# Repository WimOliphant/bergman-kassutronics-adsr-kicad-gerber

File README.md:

# bergman-kassutronics-adsr-kicad-gerber

KiCad project file and gerbers for ADSR envelope generator. 

https://www.eddybergman.com/2025/04/Kassutronic-precision-adsr.html

Currently untested. It may not work!!!

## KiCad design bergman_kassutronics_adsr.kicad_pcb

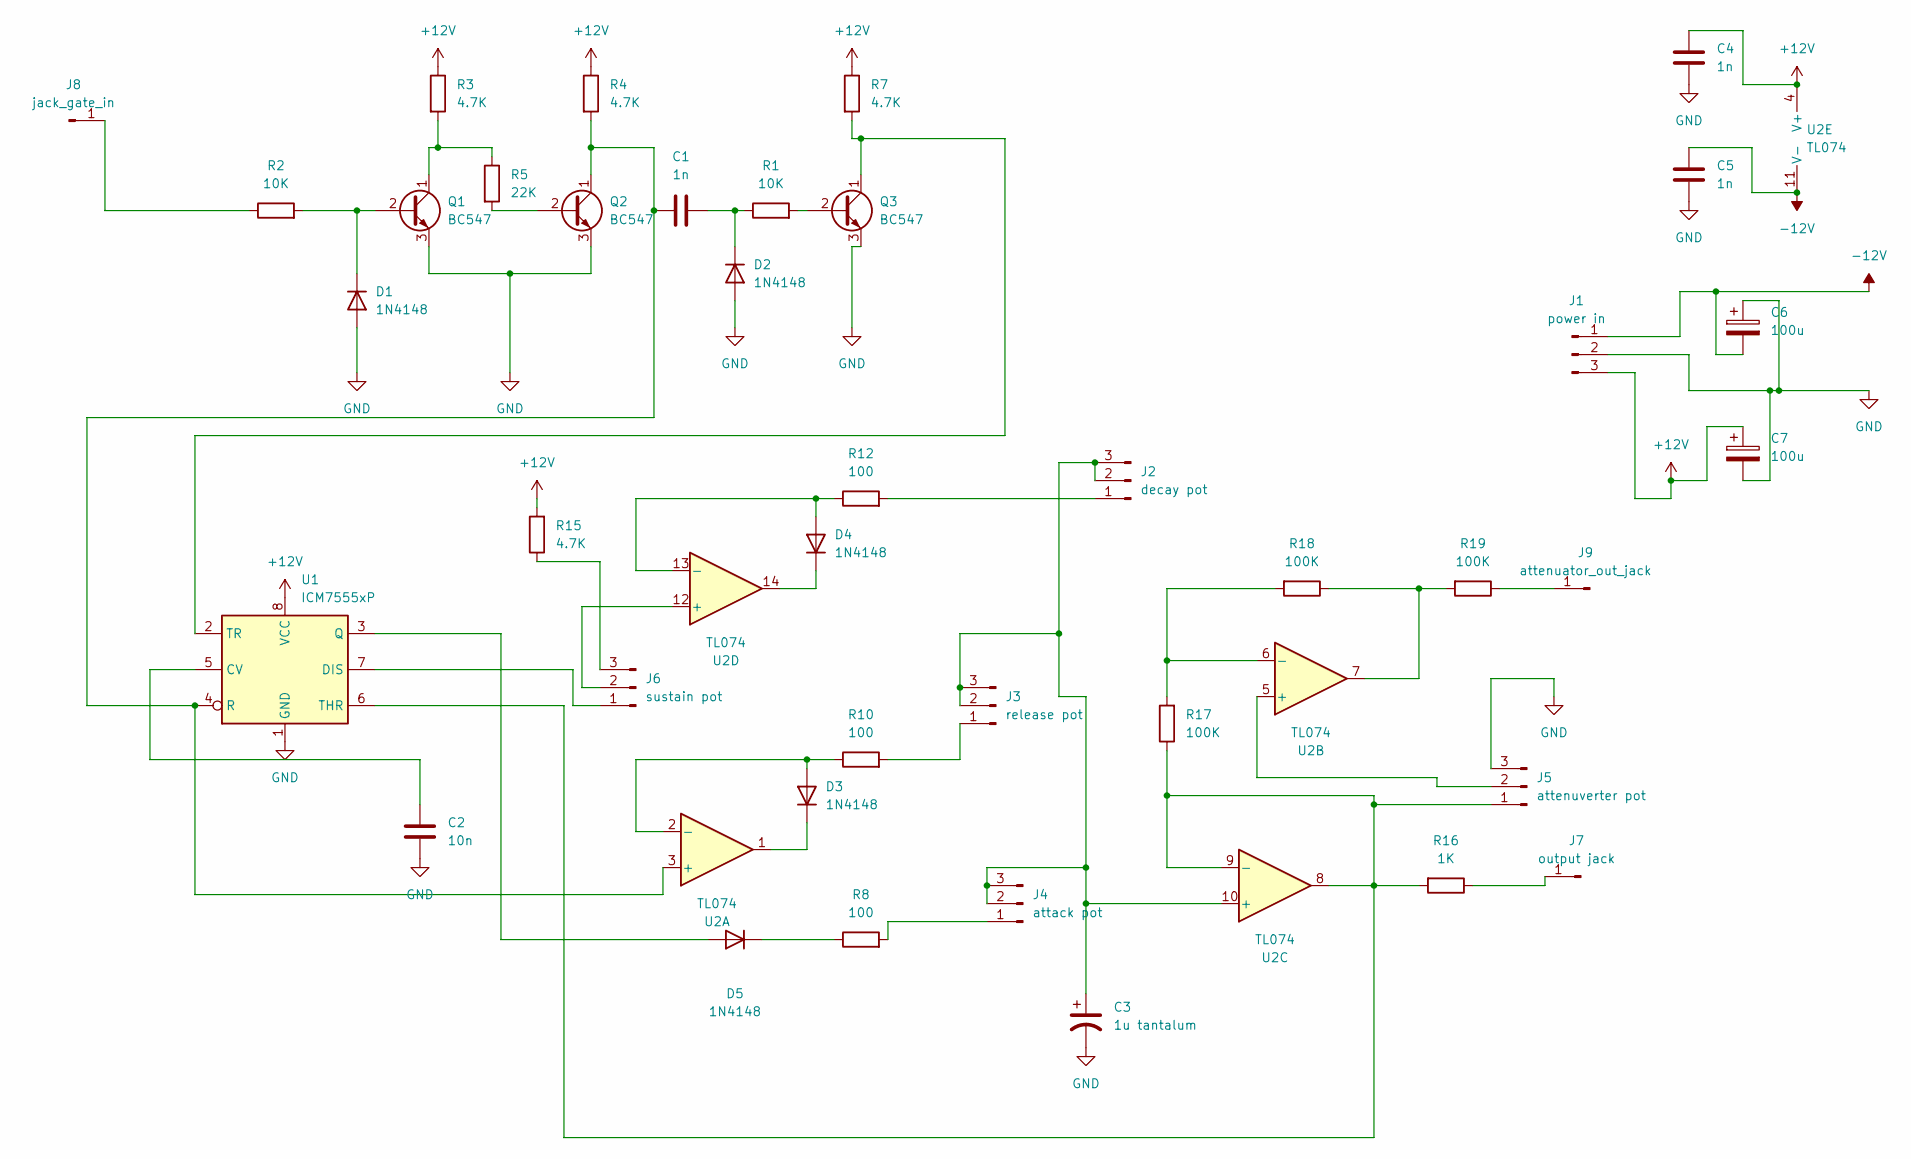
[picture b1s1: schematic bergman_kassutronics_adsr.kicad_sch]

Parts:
C1, C4, C5: 1n; C_Disc_D3.8mm_W2.6mm_P2.50mm
C2: 10n; C_Disc_D3.8mm_W2.6mm_P2.50mm
C3: 1u tantalum; C_Rect_L4.6mm_W3.8mm_P2.50mm_MKS02_FKP02
C6, C7: 100u; CP_Radial_D5.0mm_P2.50mm
D1, D2, D3, D4, D5: 1N4148; D_DO-35_SOD27_P7.62mm_Horizontal
J1: power in; Samtec_HPM-03-01-x-S_Straight_1x03_Pitch5.08mm
J2: decay pot; PinHeader_1x03_P2.54mm_Vertical
J3: release pot; PinHeader_1x03_P2.54mm_Vertical
J4: attack pot; PinHeader_1x03_P2.54mm_Vertical
J5: attenuverter pot; PinHeader_1x03_P2.54mm_Vertical
J6: sustain pot; PinHeader_1x03_P2.54mm_Vertical
J7: output jack; PinHeader_1x01_P2.54mm_Vertical
J8: jack_gate_in; PinHeader_1x01_P2.54mm_Vertical
J9: attenuator_out_jack; PinHeader_1x01_P2.54mm_Vertical
Q1, Q2, Q3: BC547; TO-92L_Inline_Wide
R1, R2: 10K; R_Axial_DIN0204_L3.6mm_D1.6mm_P7.62mm_Horizontal_wims_resis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
R3, R4, R7, R15: 4.7K; R_Axial_DIN0204_L3.6mm_D1.6mm_P7.62mm_Horizontal_wims_resis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
R5: 22K; R_Axial_DIN0204_L3.6mm_D1.6mm_P7.62mm_Horizontal_wims_resis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
R8, R10, R12: 100; R_Axial_DIN0204_L3.6mm_D1.6mm_P7.62mm_Horizontal_wims_resis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
R16: 1K; R_Axial_DIN0204_L3.6mm_D1.6mm_P7.62mm_Horizontal_wims_resis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
R17, R18, R19: 100K; R_Axial_DIN0204_L3.6mm_D1.6mm_P7.62mm_Horizontal_wims_resis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
U1: ICM7555xP; DIP-8_W7.62mm_LongPads
U2: TL074; DIP-14_W7.62mm_LongPads

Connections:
+12V: C4.1, C7.1, J1.3, R3.1, R4.1, R7.1, R15.2, U1.8 (VCC), U2.4 (V+)
-12V: C5.1, C6.2, J1.1, U2.11 (V-)
GND: C2.2, C3.2, C4.2, C5.2, C6.1, C7.2, D1.2 (A), D2.2 (A), J1.2, J5.3, Q1.3 (E), Q2.3 (E), Q3.3 (E), U1.1 (GND)
unnamed: D1.1 (K), Q1.2 (B), R2.2
unnamed: C1.2, D2.1 (K), R1.1
unnamed: D3.2 (A), R10.1, U2.2 (-)
unnamed: D3.1 (K), U2.1
unnamed: D4.2 (A), R12.1, U2.13 (-)
unnamed: D4.1 (K), U2.14
unnamed: D5.2 (A), U1.3 (Q)
unnamed: D5.1 (K), R8.1
unnamed: J2.1, R12.2
unnamed: C3.1, J2.2, J2.3, J3.2, J3.3, J4.2, J4.3, U2.10 (+)
unnamed: J3.1, R10.2
unnamed: J4.1, R8.2
unnamed: J5.1, R16.2, R17.1, U1.6 (THR), U2.8, U2.9 (-)
unnamed: J5.2, U2.5 (+)
unnamed: J6.1, U1.7 (DIS)
unnamed: J6.2, U2.12 (+)
unnamed: J6.3, R15.1
unnamed: J7.1, R16.1
unnamed: J8.1, R2.1
unnamed: J9.1, R19.1
unnamed: Q1.1 (C), R3.2, R5.1
unnamed: Q2.2 (B), R5.2
unnamed: C1.1, Q2.1 (C), R4.2, U1.4 (R), U2.3 (+)
unnamed: Q3.2 (B), R1.2
unnamed: Q3.1 (C), R7.2, U1.2 (TR)
unnamed: R18.1, R19.2, U2.7
unnamed: C2.1, U1.5 (CV)
unnamed: R17.2, R18.2, U2.6 (-)

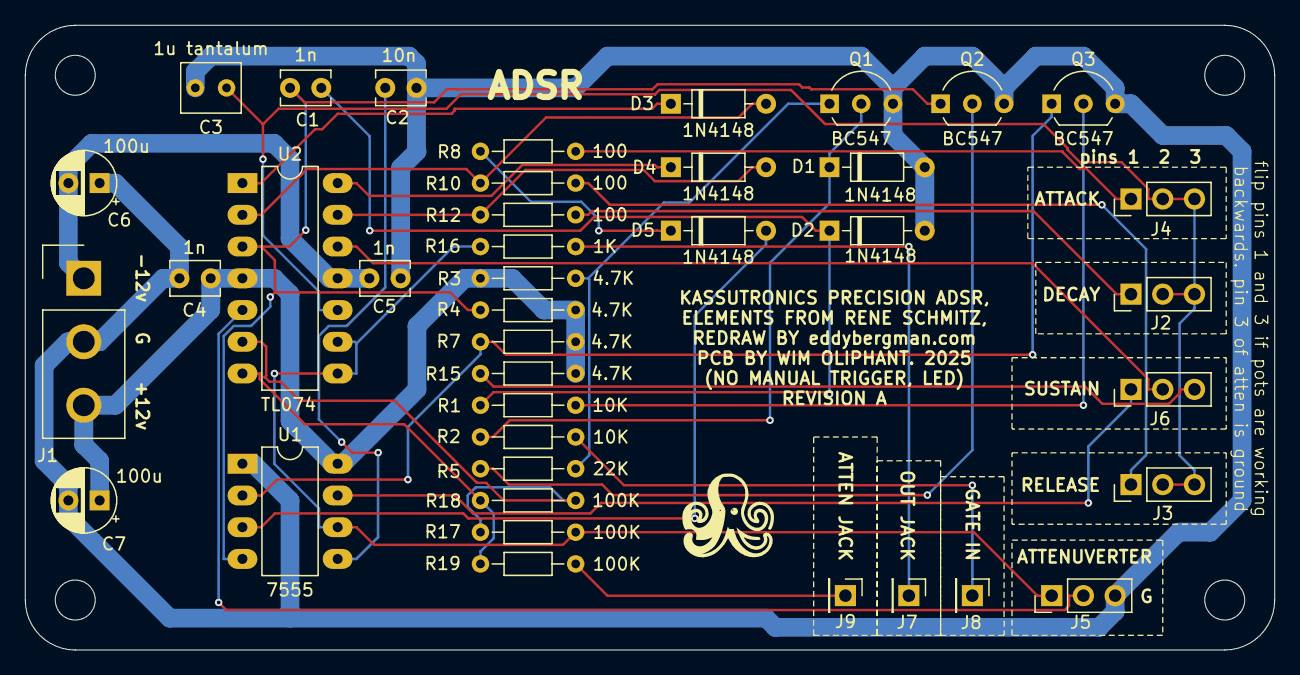
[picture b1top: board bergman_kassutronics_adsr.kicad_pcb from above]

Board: 2 copper layers, 100.0 x 50.0 mm, 44 parts (0 on the bottom side), 31 nets.

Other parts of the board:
REF1, REF2, REF3, REF4: MountingHole_3.2mm_M3

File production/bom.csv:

Designator,Footprint,Quantity,Value,LCSC Part #
"C1, C4, C5",C_Disc_D3.8mm_W2.6mm_P2.50mm,3,1n,
C2,C_Disc_D3.8mm_W2.6mm_P2.50mm,1,10n,
C3,C_Rect_L4.6mm_W3.8mm_P2.50mm_MKS02_FKP02,1,1u tantalum,
"C6, C7",CP_Radial_D5.0mm_P2.50mm,2,100u,
"D1, D2, D3, D4, D5",D_DO-35_SOD27_P7.62mm_Horizontal,5,1N4148,
J1,Samtec_HPM-03-01-x-S_Straight_1x03_Pitch5.08mm,1,power in,
J2,PinHeader_1x03_P2.54mm_Vertical,1,decay pot,
J3,PinHeader_1x03_P2.54mm_Vertical,1,release pot,
J4,PinHeader_1x03_P2.54mm_Vertical,1,attack pot,
J5,PinHeader_1x03_P2.54mm_Vertical,1,attenuverter pot,
J6,PinHeader_1x03_P2.54mm_Vertical,1,sustain pot,
J7,PinHeader_1x01_P2.54mm_Vertical,1,output jack,
J8,PinHeader_1x01_P2.54mm_Vertical,1,jack_gate_in,
J9,PinHeader_1x01_P2.54mm_Vertical,1,attenuator_out_jack,
"Q1, Q2, Q3",TO-92L_Inline_Wide,3,BC547,
"R1, R2",R_Axial_DIN0204_L3.6mm_D1.6mm_P7.62mm_Horizontal_wims_resistor1,2,10K,
"R10, R12, R8",R_Axial_DIN0204_L3.6mm_D1.6mm_P7.62mm_Horizontal_wims_resistor1,3,100,
"R15, R3, R4, R7",R_Axial_DIN0204_L3.6mm_D1.6mm_P7.62mm_Horizontal_wims_resistor1,4,4.7K,
R16,R_Axial_DIN0204_L3.6mm_D1.6mm_P7.62mm_Horizontal_wims_resistor1,1,1K,
"R17, R18, R19",R_Axial_DIN0204_L3.6mm_D1.6mm_P7.62mm_Horizontal_wims_resistor1,3,100K,
R5,R_Axial_DIN0204_L3.6mm_D1.6mm_P7.62mm_Horizontal_wims_resistor1,1,22K,
U1,DIP-8_W7.62mm_LongPads,1,7555,
U2,DIP-14_W7.62mm_LongPads,1,TL074,
